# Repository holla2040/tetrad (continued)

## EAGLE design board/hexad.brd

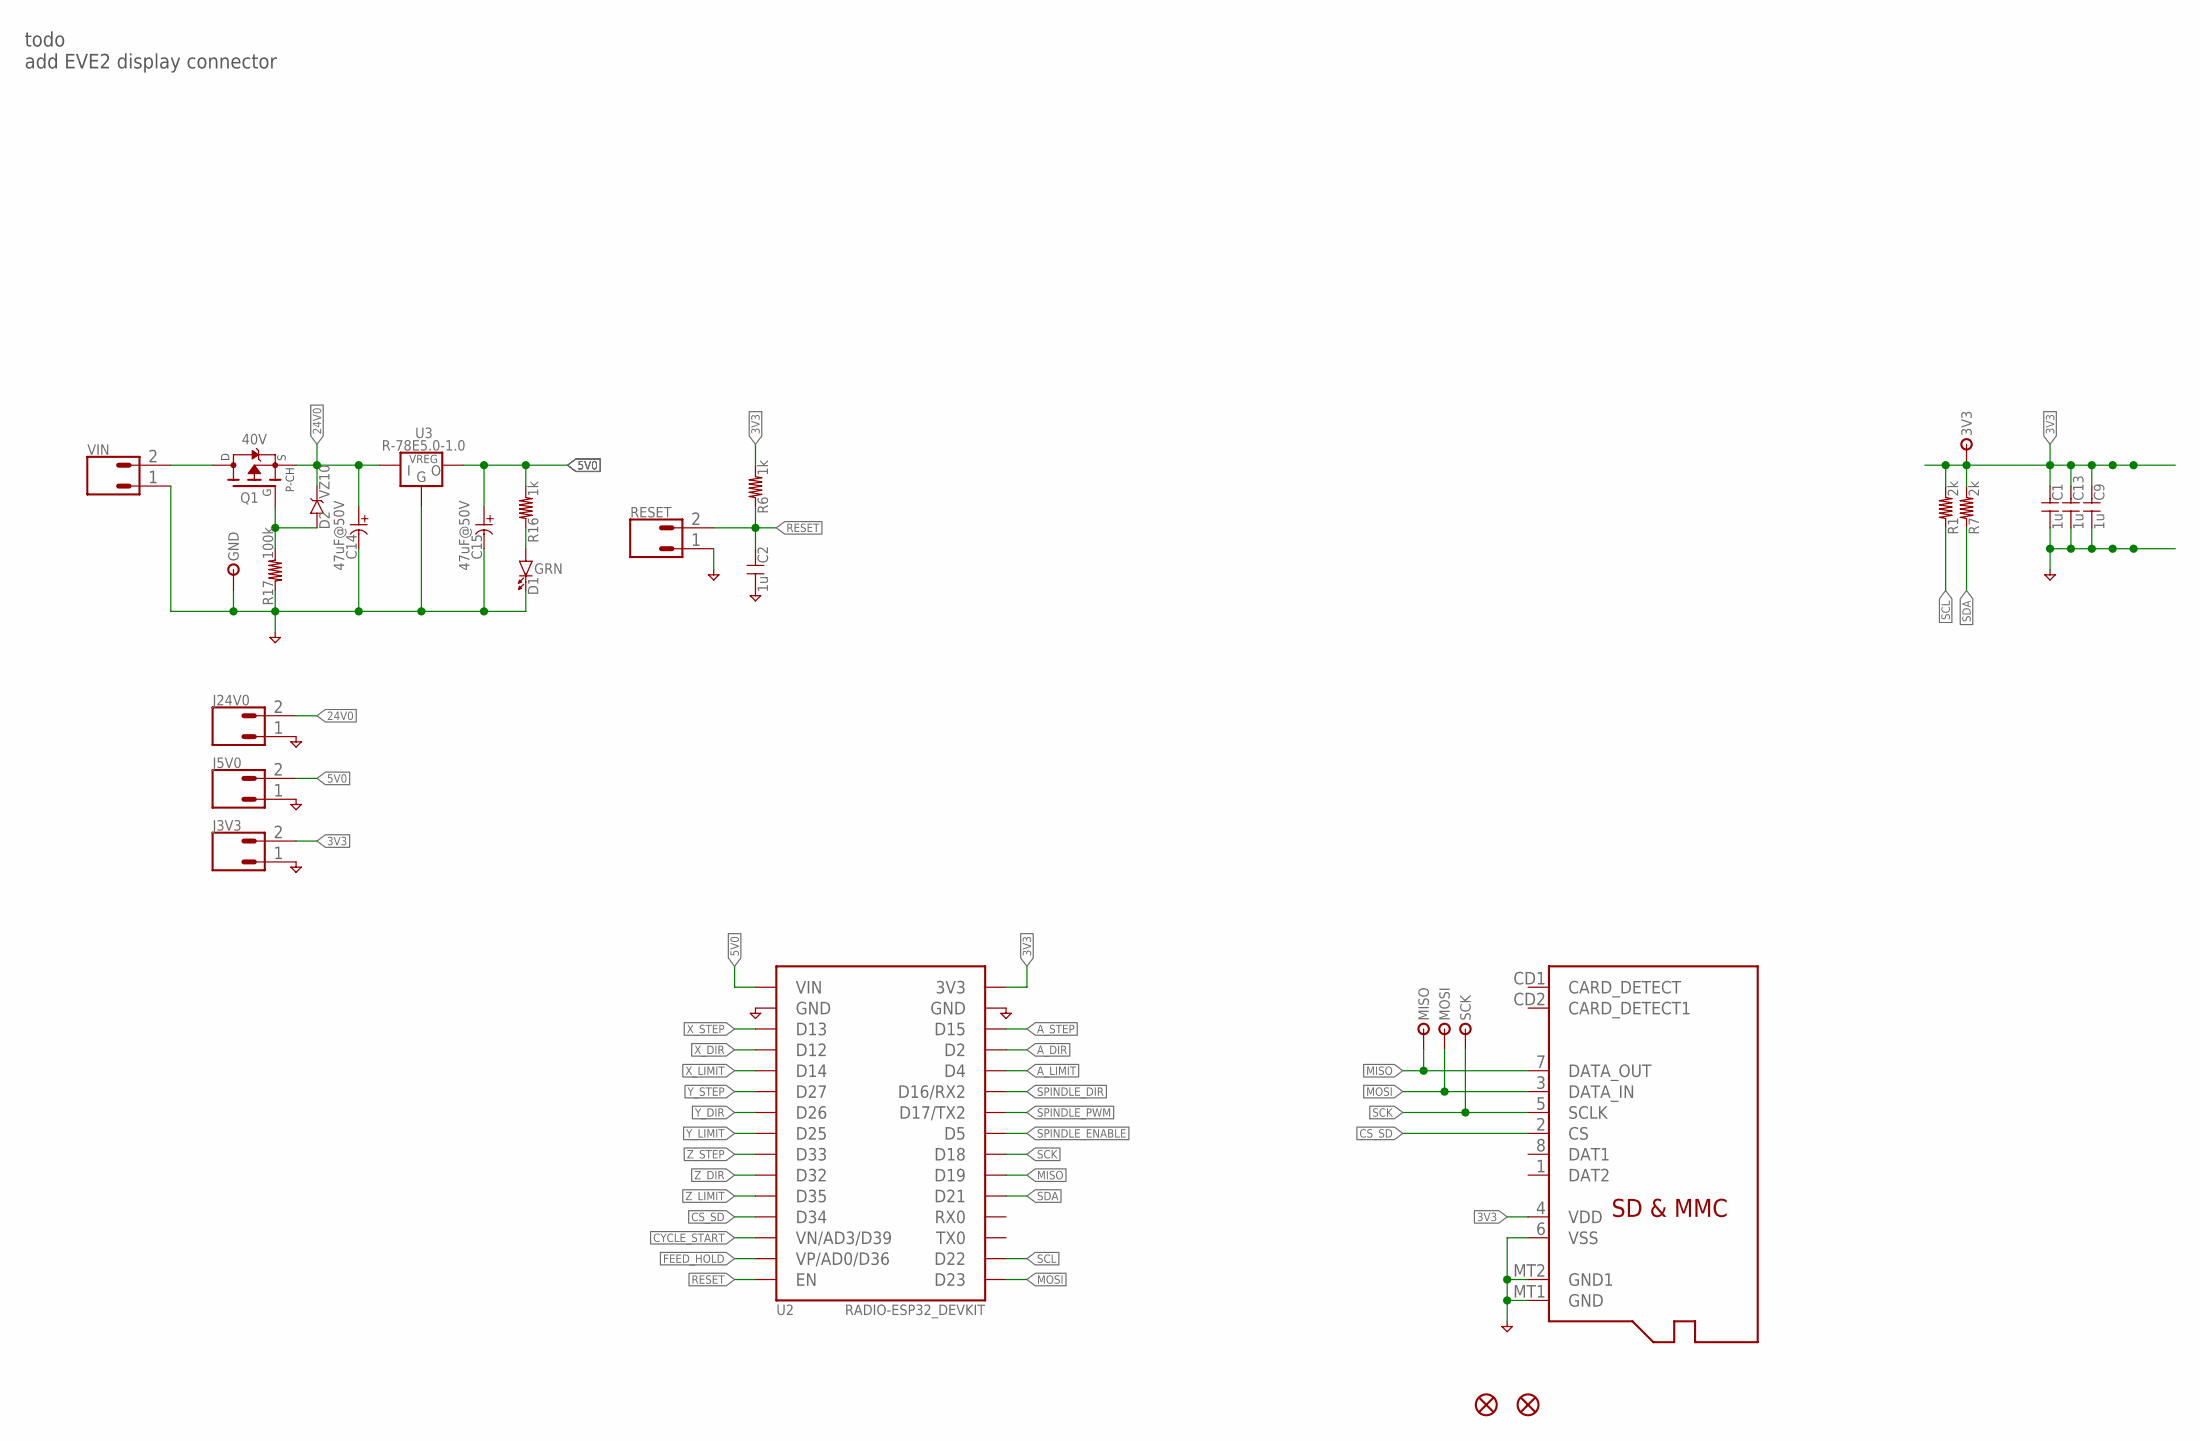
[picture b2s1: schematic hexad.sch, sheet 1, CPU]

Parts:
3V3: TESTPOINTTHRU; TPTHRU
C1, C2, C9, C13: 1u; C-0603
C14, C15: 47uF@50V; C-E-6
D1: GRN; LED-0603
D2: VZ10; D-SOD323
FID1, FID2: FIDUCIAL-MICRO
GND: TESTPOINTTHRU; TPTHRU
J1: CONN-MICROSD-2908-05WB-MG
J3V3, J5V0, J24V0: CONN-02-.100-VERT-HEADER; CONN-.100-2
MISO: TESTPOINTTHRU; TPTHRU
MOSI: TESTPOINTTHRU; TPTHRU
Q1: 40V; TO252
R1, R7: 2k; R-0603
R6, R16: 1k; R-0603
R17: 100k; R-0603
RESET: CONN-02-.100-VERT-HEADER; CONN-.100-2
SCK: TESTPOINTTHRU; TPTHRU
U2: RADIO-ESP32_DEVKIT; ESP32_DEVKIT
U3: R-78E5.0-1.0; VREG-SIP3
VIN: CONN-02-3.81MM-PLUGIN-SCREW; CONN-3.81MM-KF2EDG-2

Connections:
3V3: 3V3.1, C1.2, C9.2, C13.2, J1.4 (VDD), J3V3.2, R1.2, R6.2, R7.2, U2.3V3; also elsewhere on the board
5V0: C15.+, J5V0.2, R16.2, U2.VIN, U3.3 (VOUT); also elsewhere on the board
24V0: C14.+, D2.C, J24V0.2, Q1.2 (S), U3.1 (VIN); also elsewhere on the board
A_DIR: U2.D2; also elsewhere on the board
A_LIMIT: U2.D4; also elsewhere on the board
A_STEP: U2.D15; also elsewhere on the board
CS_SD: J1.2 (CS), U2.D34
CYCLE_START: U2.VN (VN/AD3/D39); also elsewhere on the board
FEED_HOLD: U2.VP (VP/AD0/D36); also elsewhere on the board
GND: C1.1, C2.1, C9.1, C13.1, C14.-, C15.-, D1.C, GND.1, J1.6 (VSS), J1.MT1 (GND), J1.MT2 (GND1), J3V3.1, J5V0.1, J24V0.1, R17.1, RESET.1, U2.GND@1 (GND), U2.GND@2 (GND), U3.2 (GND), VIN.1; also elsewhere on the board
MISO: J1.7 (DATA_OUT), MISO.1, U2.D19
MOSI: J1.3 (DATA_IN), MOSI.1, U2.D23; also elsewhere on the board
unnamed: Q1.3 (D), VIN.2
unnamed: D2.A, Q1.1 (G), R17.2
unnamed: D1.A, R16.1
RESET: C2.2, R6.1, RESET.2, U2.EN; also elsewhere on the board
SCK: J1.5 (SCLK), SCK.1, U2.D18; also elsewhere on the board
SCL: R1.1, U2.D22; also elsewhere on the board
SDA: R7.1, U2.D21; also elsewhere on the board
SPINDLE_DIR: U2.RX2 (D16/RX2); also elsewhere on the board
SPINDLE_ENABLE: U2.D5; also elsewhere on the board
SPINDLE_PWM: U2.TX2 (D17/TX2); also elsewhere on the board
X_DIR: U2.D12; also elsewhere on the board
X_LIMIT: U2.D14; also elsewhere on the board
X_STEP: U2.D13; also elsewhere on the board
Y_DIR: U2.D26; also elsewhere on the board
Y_LIMIT: U2.D25; also elsewhere on the board
Y_STEP: U2.D27; also elsewhere on the board
Z_DIR: U2.D32; also elsewhere on the board
Z_LIMIT: U2.D35; also elsewhere on the board
Z_STEP: U2.D33; also elsewhere on the board

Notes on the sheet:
todo add EVE2 display connector

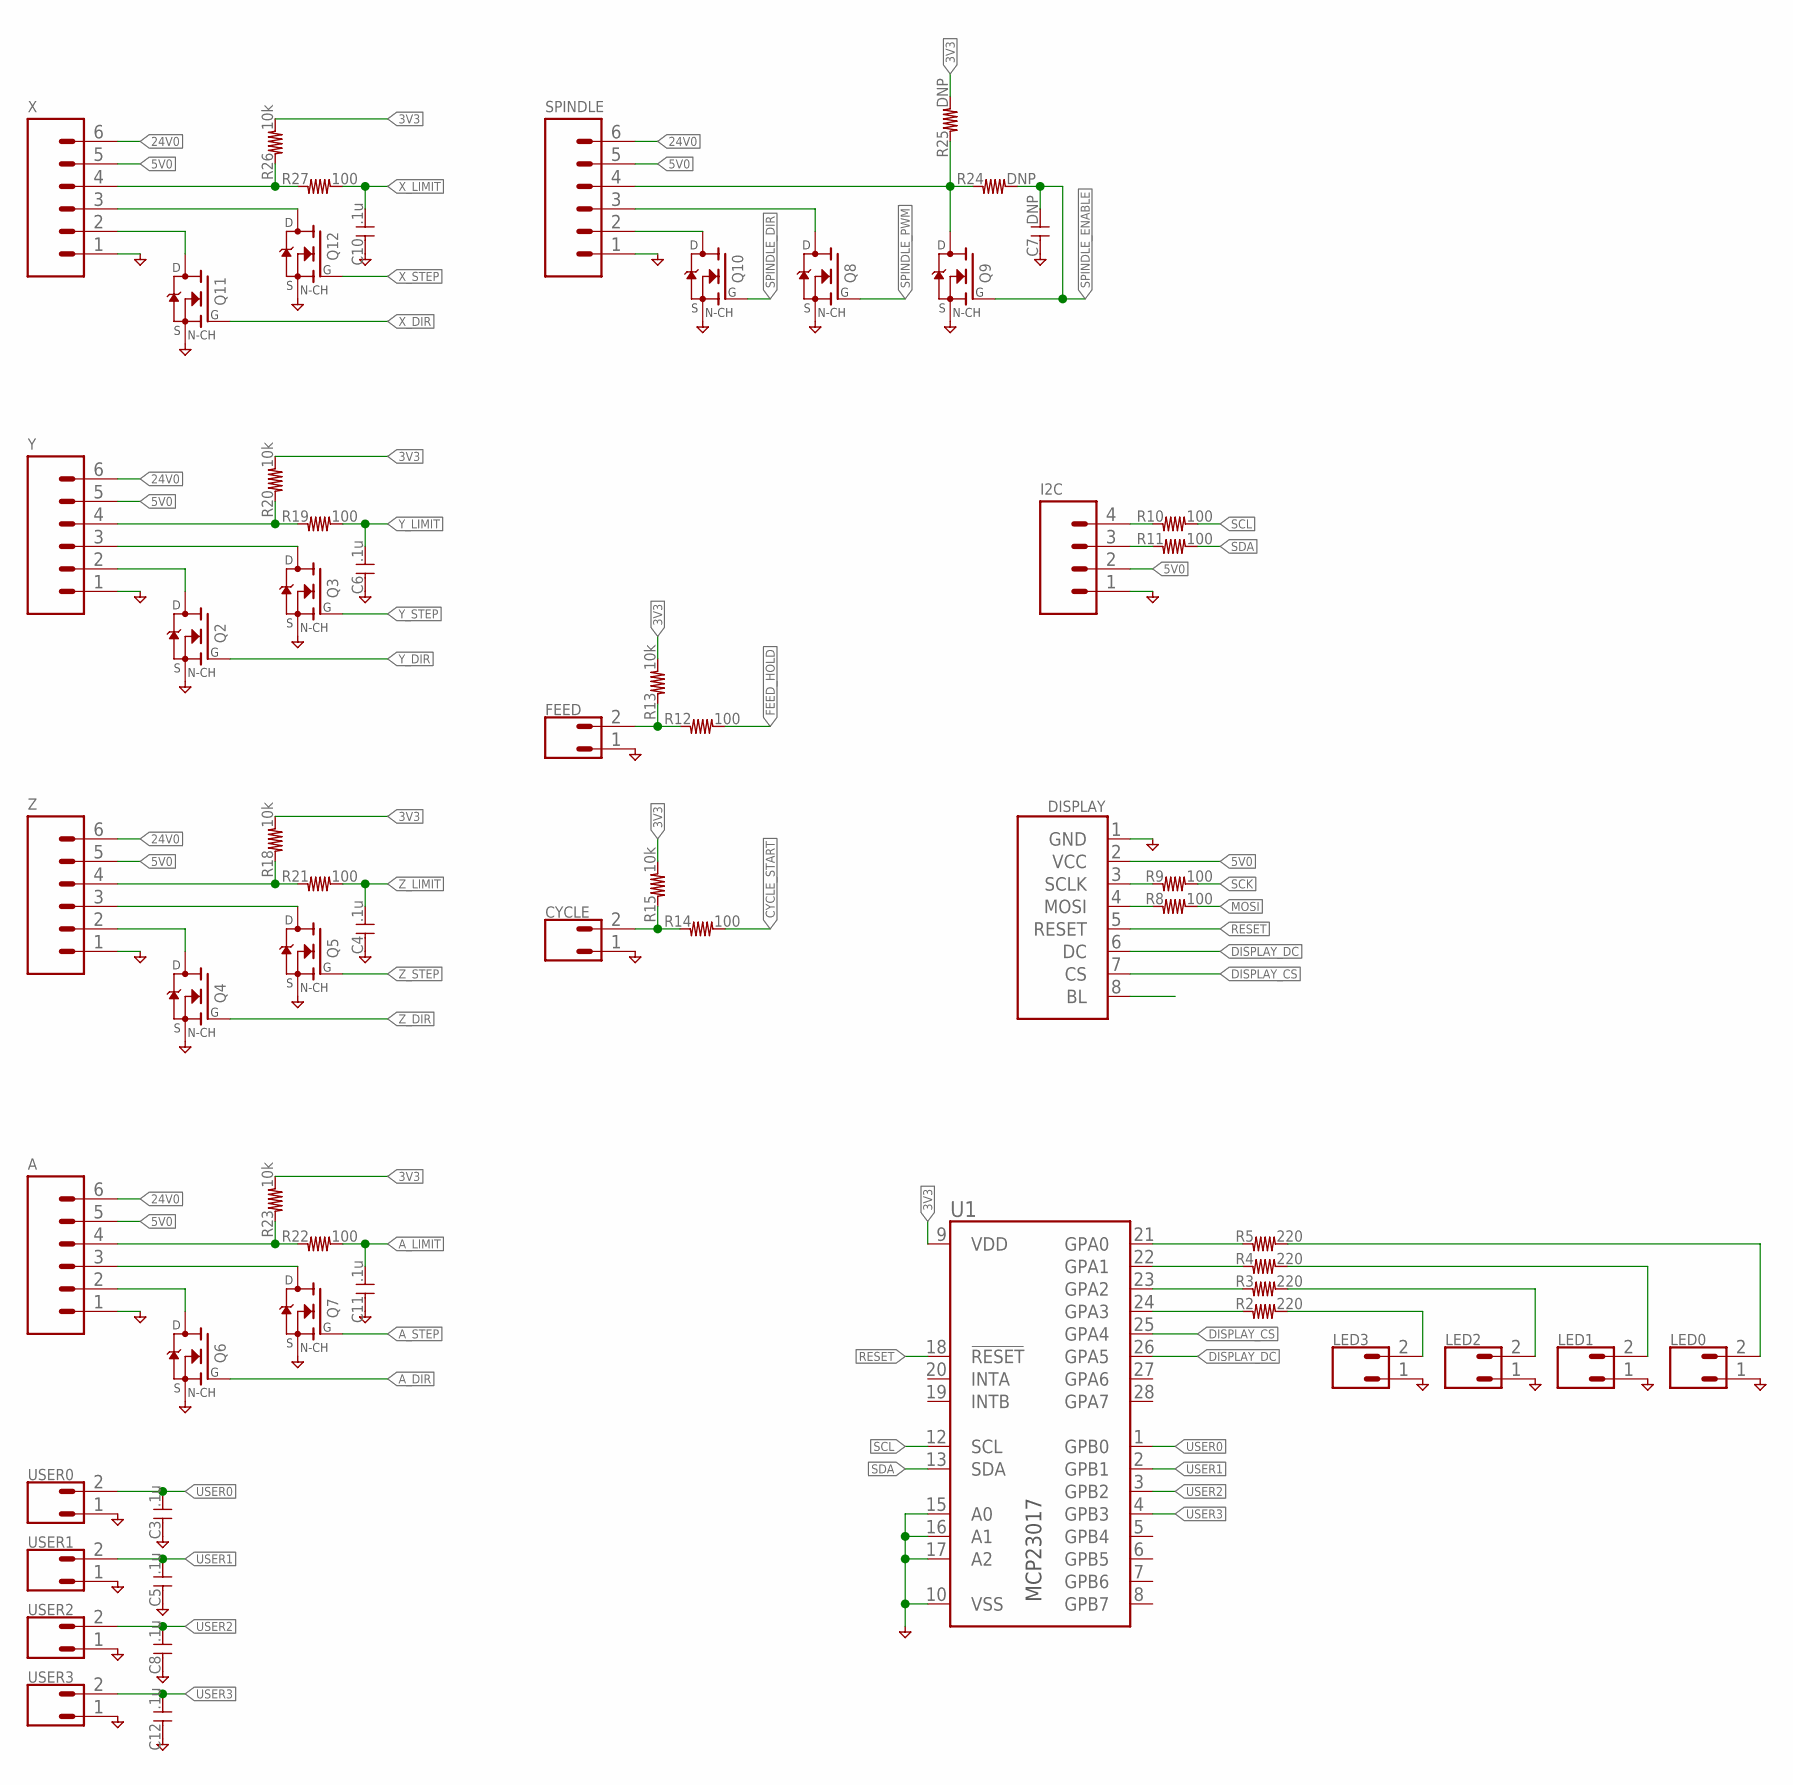
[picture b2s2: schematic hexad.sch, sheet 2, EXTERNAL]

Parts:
A: CONN-06-.100-VERT-HEADER; CONN-.100-6
C3, C4, C5, C6, C8, C10, C11, C12: .1u; C-0603
C7: DNP; C-0603
CYCLE: CONN-02-.100-VERT-HEADER; CONN-.100-2
DISPLAY: DISP-SPI-TFT-128X160-ST7735; 1X08
FEED: CONN-02-.100-VERT-HEADER; CONN-.100-2
I2C: CONN-04-.100-VERT-HEADER; CONN-.100-4
LED0, LED1, LED2, LED3: CONN-02-.100-VERT-HEADER; CONN-.100-2
Q2, Q3, Q4, Q5, Q6, Q7, Q8, Q9, Q10, Q11, Q12: FET-NCH-SOT23; SOT23-3
R2, R3, R4, R5: 220; R-0603
R8, R9, R10, R11, R12, R14, R19, R21, R22, R27: 100; R-0603
R13, R15, R18, R20, R23, R26: 10k; R-0603
R24, R25: DNP; R-0603
SPINDLE: CONN-06-.100-VERT-HEADER; CONN-.100-6
U1: IO-MCP23017SO; SO28W
USER0, USER1, USER2, USER3: CONN-02-.100-VERT-HEADER; CONN-.100-2
X: CONN-06-.100-VERT-HEADER; CONN-.100-6
Y: CONN-06-.100-VERT-HEADER; CONN-.100-6
Z: CONN-06-.100-VERT-HEADER; CONN-.100-6

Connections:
3V3: R13.2, R15.2, R18.2, R20.2, R23.2, R25.2, R26.2, U1.9 (VDD); also elsewhere on the board
5V0: A.5, DISPLAY.2 (VCC), I2C.2, SPINDLE.5, X.5, Y.5, Z.5; also elsewhere on the board
24V0: A.6, SPINDLE.6, X.6, Y.6, Z.6; also elsewhere on the board
A_DIR: Q6.1 (G); also elsewhere on the board
A_LIMIT: C11.1, R22.2; also elsewhere on the board
A_STEP: Q7.1 (G); also elsewhere on the board
CYCLE_START: R14.2; also elsewhere on the board
DISPLAY_CS: DISPLAY.7 (CS), U1.25 (GPA4)
DISPLAY_DC: DISPLAY.6 (DC), U1.26 (GPA5)
FEED_HOLD: R12.2; also elsewhere on the board
GND: A.1, C3.2, C4.2, C5.2, C6.2, C7.2, C8.2, C10.2, C11.2, C12.2, CYCLE.1, DISPLAY.1 (GND), FEED.1, I2C.1, LED0.1, LED1.1, LED2.1, LED3.1, Q2.2 (S), Q3.2 (S), Q4.2 (S), Q5.2 (S), Q6.2 (S), Q7.2 (S), Q8.2 (S), Q9.2 (S), Q10.2 (S), Q11.2 (S), Q12.2 (S), SPINDLE.1, U1.10 (VSS), U1.15 (A0), U1.16 (A1), U1.17 (A2), USER0.1, USER1.1, USER2.1, USER3.1, X.1, Y.1, Z.1; also elsewhere on the board
MOSI: R8.2; also elsewhere on the board
unnamed: R26.1, R27.1, X.4
unnamed: DISPLAY.3 (SCLK), R9.1
unnamed: DISPLAY.4 (MOSI), R8.1
unnamed: Q11.3 (D), X.2
unnamed: R19.1, R20.1, Y.4
unnamed: Q2.3 (D), Y.2
unnamed: R18.1, R21.1, Z.4
unnamed: Q4.3 (D), Z.2
unnamed: A.4, R22.1, R23.1
unnamed: A.2, Q6.3 (D)
unnamed: R5.1, U1.21 (GPA0)
unnamed: Q9.3 (D), R24.1, R25.1, SPINDLE.4
unnamed: Q10.3 (D), SPINDLE.2
unnamed: R4.1, U1.22 (GPA1)
unnamed: FEED.2, R12.1, R13.1
unnamed: CYCLE.2, R14.1, R15.1
unnamed: I2C.4, R10.1
unnamed: I2C.3, R11.1
unnamed: R3.1, U1.23 (GPA2)
unnamed: R2.1, U1.24 (GPA3)
unnamed: LED3.2, R2.2
unnamed: LED2.2, R3.2
unnamed: LED1.2, R4.2
unnamed: LED0.2, R5.2
RESET: DISPLAY.5 (RESET), U1.18 (!RESET); also elsewhere on the board
SCK: R9.2; also elsewhere on the board
SCL: R10.2, U1.12 (SCL); also elsewhere on the board
SDA: R11.2, U1.13 (SDA); also elsewhere on the board
SPINDLE_DIR: Q10.1 (G); also elsewhere on the board
SPINDLE_ENABLE: C7.1, Q9.1 (G), R24.2; also elsewhere on the board
SPINDLE_PWM: Q8.1 (G); also elsewhere on the board
USER0: C3.1, U1.1 (GPB0), USER0.2
USER1: C5.1, U1.2 (GPB1), USER1.2
USER2: C8.1, U1.3 (GPB2), USER2.2
USER3: C12.1, U1.4 (GPB3), USER3.2
X_DIR: Q11.1 (G); also elsewhere on the board
X_LIMIT: C10.1, R27.2; also elsewhere on the board
X_STEP: Q12.1 (G); also elsewhere on the board
X_STEP_5V0: Q12.3 (D), X.3
X_STEP_5V1: Q3.3 (D), Y.3
X_STEP_5V2: Q5.3 (D), Z.3
X_STEP_5V3: A.3, Q7.3 (D)
X_STEP_5V4: Q8.3 (D), SPINDLE.3
Y_DIR: Q2.1 (G); also elsewhere on the board
Y_LIMIT: C6.1, R19.2; also elsewhere on the board
Y_STEP: Q3.1 (G); also elsewhere on the board
Z_DIR: Q4.1 (G); also elsewhere on the board
Z_LIMIT: C4.1, R21.2; also elsewhere on the board
Z_STEP: Q5.1 (G); also elsewhere on the board

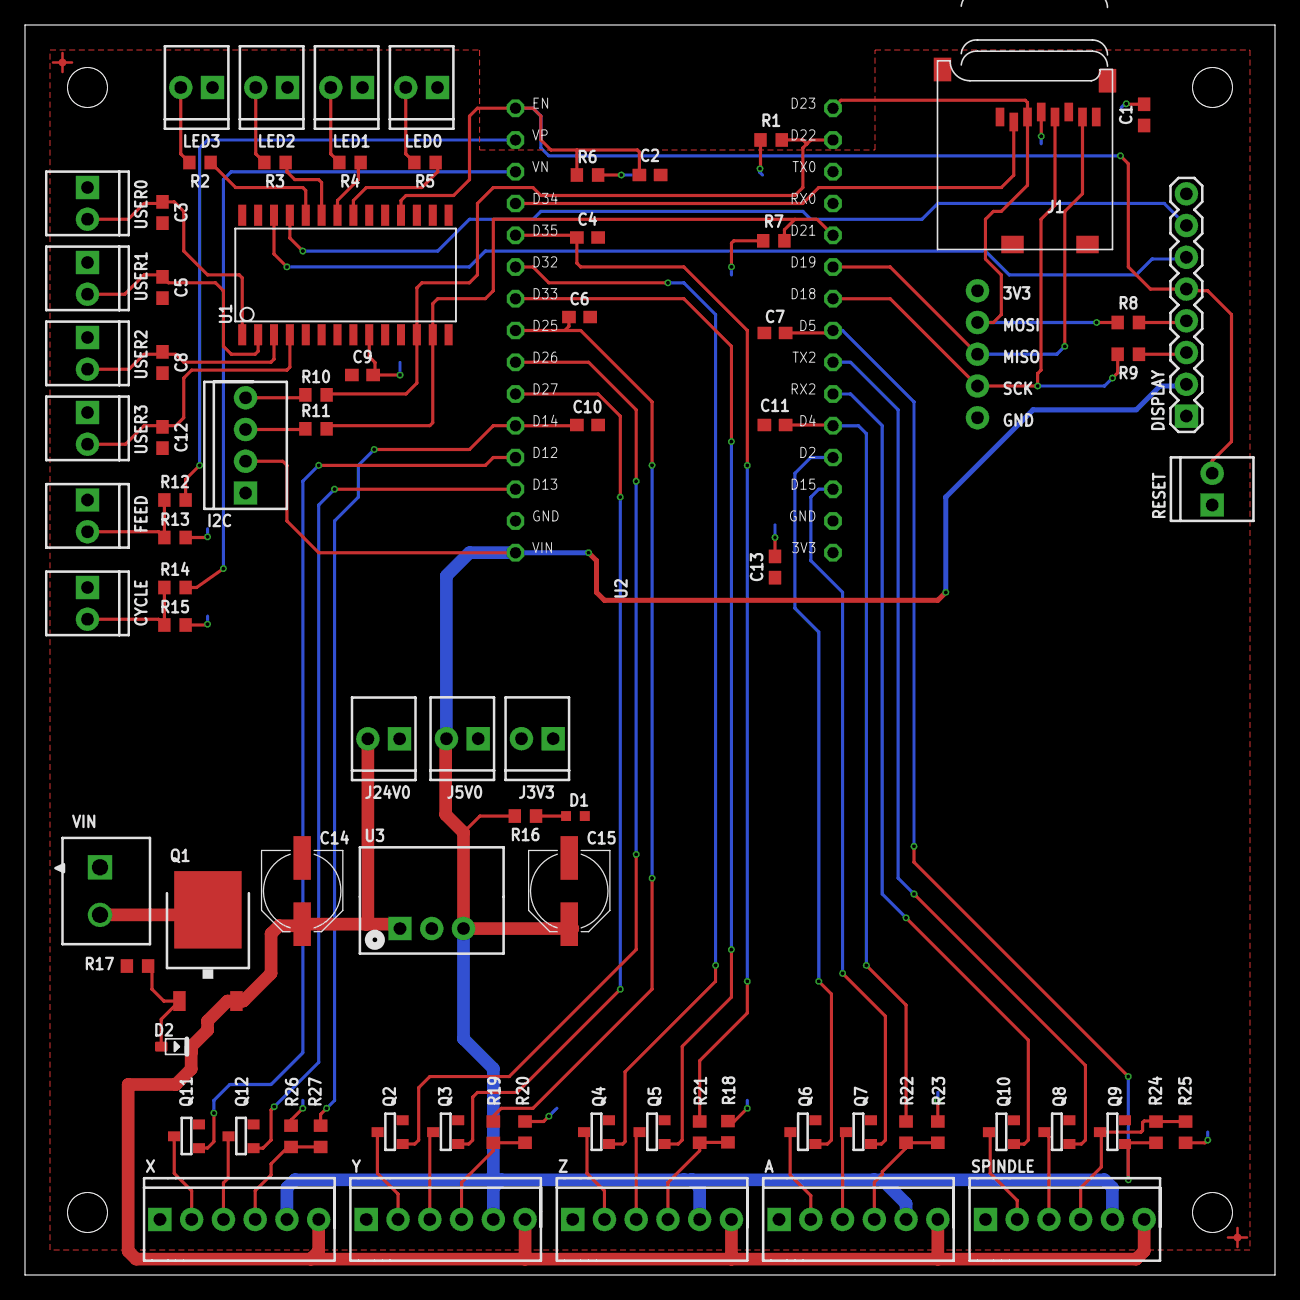
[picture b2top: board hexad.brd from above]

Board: 2 copper layers, 100.0 x 100.0 mm, 89 parts (0 on the bottom side), 66 nets.

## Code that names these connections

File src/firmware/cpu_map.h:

/*
  cpu_map.h - Header for system level commands and real-time processes
  Part of Grbl
  Copyright (c) 2014-2016 Sungeun K. Jeon for Gnea Research LLC
    
    2018 -  Bart Dring This file was modified for use on the ESP32
                    CPU. Do not use this with Grbl for atMega328P
    
  Grbl is free software: you can redistribute it and/or modify
  it under the terms of the GNU General Public License as published by
  the Free Software Foundation, either version 3 of the License, or
  (at your option) any later version.
  Grbl is distributed in the hope that it will be useful,
  but WITHOUT ANY WARRANTY; without even the implied warranty of
  MERCHANTABILITY or FITNESS FOR A PARTICULAR PURPOSE.  See the
  GNU General Public License for more details.
  You should have received a copy of the GNU General Public License
  along with Grbl.  If not, see <http://www.gnu.org/licenses/>.
*/

#ifndef cpu_map_h
#define cpu_map_h 

  /*
    Not all pins can can work for all functions.
    Check features like pull-ups, pwm, etc before
  re-assigning numbers
    
    (gpio34-39) are inputs only and don't have software pullup/down functions
    You MUST use external pull-ups or noise WILL cause problems.
    
    Unlike the AVR version certain pins are not forced into the same port. 
    Therefore, bit masks are not use the same way and typically should not be 
    changed. They are just preserved right now to make it easy to stay in sync
    with AVR grbl
    
    */
    
//Set your pin definition 
//let -1 to use default board pin
#define GRBL_SPI_SS -1
#define GRBL_SPI_MOSI -1
#define GRBL_SPI_MISO -1
#define GRBL_SPI_SCK -1
//Set your frequency 
#define GRBL_SPI_FREQ  4000000


// ================= common to all machines ================================

// These are some ESP32 CPU Settings that the program needs, but are generally not changed
#define F_TIMERS    80000000    // a reference to the speed of ESP32 timers
#define F_STEPPER_TIMER 20000000  // frequency of step pulse timer
#define STEPPER_OFF_TIMER_PRESCALE 8 // gives a frequency of 10MHz
#define STEPPER_OFF_PERIOD_uSEC  3  // each tick is

#define STEP_PULSE_MIN 2   // uSeconds
#define STEP_PULSE_MAX 10  // uSeconds

// =============== Don't change or comment these out ======================
// They are for legacy purposes and will not affect your I/O 

#define X_STEP_BIT    0  // don't change
#define Y_STEP_BIT    1  // don't change
#define Z_STEP_BIT    2  // don't change        
#define A_STEP_BIT    3  // don't change
#define B_STEP_BIT    4  // don't change
#define C_STEP_BIT    5  // don't change
#define STEP_MASK       B111111 // don't change

#define X_DIRECTION_BIT   0 // don't change
#define Y_DIRECTION_BIT   1  // don't change
#define Z_DIRECTION_BIT   2  // don't change
#define A_DIRECTION_BIT   3 // don't change
#define B_DIRECTION_BIT   4  // don't change
#define C_DIRECTION_BIT   5  // don't change

#define X_LIMIT_BIT         0  // don't change
#define Y_LIMIT_BIT         1  // don't change
#define Z_LIMIT_BIT         2  // don't change
#define A_LIMIT_BIT         3  // don't change
#define B_LIMIT_BIT         4  // don't change
#define C_LIMIT_BIT         5  // don't change      

#define PROBE_MASK        1 // don't change     

#define CONTROL_MASK        B1111   // don't change

// =======================================================================
        



#ifdef CPU_MAP_TETRAD

#define USE_RMT_STEPS

#define X_RMT_CHANNEL       0
#define X_DIRECTION_PIN     GPIO_NUM_12
#define X_STEP_PIN          GPIO_NUM_13
#define X_LIMIT_PIN         GPIO_NUM_14
#define DEFAULT_X_MAX_RATE  4000

#define Y_RMT_CHANNEL       1
#define Y_DIRECTION_PIN     GPIO_NUM_26
#define Y_STEP_PIN          GPIO_NUM_27
#define Y_LIMIT_PIN         GPIO_NUM_25
#define DEFAULT_Y_MAX_RATE  4000

#define Z_RMT_CHANNEL       2
#define Z_DIRECTION_PIN     GPIO_NUM_32
#define Z_STEP_PIN          GPIO_NUM_33
#define Z_LIMIT_PIN         GPIO_NUM_35
#define DEFAULT_Z_MAX_RATE  4000

#define A_RMT_CHANNEL       3
#define A_DIRECTION_PIN     GPIO_NUM_2
#define A_STEP_PIN          GPIO_NUM_15
#define A_LIMIT_PIN         GPIO_NUM_4
#define DEFAULT_A_MAX_RATE  4000


#define SPINDLE_PWM_PIN           GPIO_NUM_17
#define SPINDLE_DIR_PIN           GPIO_NUM_16
#define SPINDLE_ENABLE_PIN        GPIO_NUM_5
#define SPINDLE_PWM_BIT_PRECISION 8
#define SPINDLE_PWM_MAX_VALUE     255
#define SPINDLE_PWM_MIN_VALUE     1
#define SPINDLE_PWM_CHANNEL       0
#define SPINDLE_PWM_OFF_VALUE     0
#define SPINDLE_PWM_BASE_FREQ     5000


#define LIMIT_MASK          B0111

#endif 


#endif

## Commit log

2019-11-01 initial add
2019-11-01 added reference
2019-11-01 got it working
2019-11-01 updated makefile
2019-11-01 added more parts
2019-11-01 started routing
2019-11-01 changed connectors to 0.1 headers
2019-11-02 release v1.0
2019-11-02 corrected readme
2019-11-12 added todo to schematic
2019-11-12 moved a few things around on the schematic
2019-11-13 started work on v1.1
2019-11-13 removing this due to personal info
2019-11-18 updated schematic
2019-11-18 started fixing board mistakes
2019-11-18 beefed up 24v0 traces
2019-11-20 starting add drv8825 slots and micro-fit connectors
2019-11-23 selected hammond enclosure and larger board
2019-11-23 started initial positioning
2019-11-24 started placement of X
2019-11-24 continued working on placement
2019-12-09 XYZ tested # Please enter the commit message for your changes. Lines starting
2019-12-21 x,y,z,a hardware checked out
2019-12-21 checked out the spindle hardware started to simplify the motor part of schematic
2020-02-02 schematic updated alot moving to bud PN-1325-DGMB enclosure initial add for others
